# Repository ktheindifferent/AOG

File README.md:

# AOG · Grow observatory

A Raspberry Pi controller for observing a grow system and controlling its equipment. AOG v2 combines a local HTTPS dashboard, air and water sensor history, pH calibration, cameras, schedules, and four assignable relay outputs.

## Dashboard

- **Overview:** air and water temperatures, air quality, pH history, overflow status, and equipment.
- **Connections:** Arduino identification, individual sensor health, pin maps, raw readings, RAM buffer status, and firmware management.
- **Sensor history:** eight metrics with 1-hour, 6-hour, 24-hour, and 7-day views. Water probes keep stable D6/D8 history keys.
- **Reports:** full-resolution CSV/JSON and printable HTML reports, including both water temperatures.
- **Equipment:** independent relays, lighting and watering schedules, configurable overflow stops, and Stop all.

The interface uses local assets and works on desktop and mobile. A reporting Arduino and a physically verified sensor are distinct states. Open overflow contacts can mean high water **or** a disconnected wire; analog pH/gas readings cannot prove physical connection.

## Build and run

Use Rust 1.89 or newer on Raspberry Pi OS / Debian. From the repository root:

```sh
sh setup.sh
cargo build --locked --release -j1
sudo install -m 755 target/release/aog /usr/local/bin/aog-v2.new
sudo mv /usr/local/bin/aog-v2.new /usr/local/bin/aog-v2
sudo install -m 644 deploy/aog-v2.service /etc/systemd/system/aog-v2.service
sudo systemctl daemon-reload
sudo systemctl enable aog-v2
sudo systemctl restart aog-v2
```

Open `https://<pi-address>:8443` and sign in as `admin` using the installation password. Existing settings, passwords, certificates, and recorded data remain in `/opt/aog`. See [controller operation and password recovery](docs/controller.md) and [network configuration](SECURITY.md).

The build automatically embeds current `www/` assets and `firmware/package/`. Rebuilding and installing the controller also installs its firmware package.

## Arduino firmware and water probes

[Sensor Kit](firmware/sensor-kit/sensor-kit.ino) and [Dual OVF](firmware/dual-ovf/dual-ovf.ino) include Nano, Nano old-bootloader, and Uno ATmega328P binaries. Install upload tools on the Pi:

```sh
bash deploy/install-firmware-tools.sh
```

Open **Connections → Firmware**, select the identified Arduino and its actual board profile. AOG pauses schedules, verifies outputs are off, drains supported RAM logs, flashes the checksum-verified package, and waits for the new version to reconnect. Schedules remain paused afterward. Installing AOG or the tools does not flash boards.

The installed three-wire water probes are **not yet identified**. Firmware detects externally powered DS18B20 family `0x28` probes on **D6 and D8 on either Arduino**, verifies CRCs, and exposes each source board and ROM. It does not assume tank assignments. Name and bind probes after identifying them. [Wiring and troubleshooting](docs/wiring.md).

The [Nano carrier PCB](hardware/nano-carrier/README.md) provides removable Nano
sockets, fitted water-probe pull-ups, labeled sensor terminals and CCS811 level
shifting. One common design serves Sensor Kit and Dual OVF. Its prototype
manufacturing/assembly package and small-order instructions are included;
physical hardware qualification is still required.

Each Arduino retains **24 one-minute records in RAM**. The Pi acknowledges a record only after syncing it to disk. Deduplicated replays feed environmental/water history and the pH chart. Original timestamps, raw fields, boot IDs, and sequences can be downloaded from Connections. RAM does not survive resets, flashing, or power loss. A full ring replaces its oldest record and reports drops. USB hardware may reset a board during a Pi reboot even when normal service reconnects preserve it. [Protocol and recovery](docs/firmware-protocol.md).

## Repository

```text
src/                 Rust v2 controller
www/                 Dashboard, local fonts, and vector artwork
firmware/            Arduino sources, build script, tests, and release package
hardware/            Nano carrier PCB, assembly package, and ordering guide
deploy/              systemd service and upload-tool installer
tests/               Backend and browser regression tests
docs/                Operation, wiring, and protocol documentation
```

The Python v1 application, old measurements/media, unused web template, and obsolete notes are removed from the current tree. Previous versions remain in Git history. On-device history schemas remain readable; repository cleanup does not erase runtime data.

[Testing](TESTING.md) · [Firmware builds](firmware/README.md) · [Publishing instructions](docs/publishing.md) · [Existing GitHub repository](https://github.com/PixelCoda/AOG) · [Releases](https://github.com/PixelCoda/AOG/releases)

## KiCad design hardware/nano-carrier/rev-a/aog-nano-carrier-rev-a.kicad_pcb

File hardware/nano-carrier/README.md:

# AOG Nano carrier · revision A

One **80 × 80 mm PCB design**, used twice: plug a Sensor Kit Nano into one
assembled carrier and a Dual OVF Nano into the other. Both carriers use the
same complete parts list, so a two-board order needs only one design and one
assembly setup. Firmware selects the role; there is no hardware mode jumper.

**This is a first prototype design. It has not been manufactured or bench
tested.** Electrical design-rule and connectivity results are in
[rev-a/drc.txt](rev-a/drc.txt) and the release validation file. The water-probe
model and CCS811 breakout remain unidentified; compatibility conditions below
are part of this design, not verified facts about those modules.

## Order the assembled boards

Start with [ORDERING.md](ORDERING.md). Order **two identical, fully populated
carriers**, including the female Nano sockets and screw terminals. The package
contains fabrication Gerbers/drills, a manufacturer-specific BOM, placement
coordinates, editable KiCad files, assembly drawings and a bench-test procedure.
No order has been submitted.

The Nanos and external sensors are reused and are **not included in the
assembly BOM**. The assembler installs the carrier's parts. After delivery you
plug in the Nanos and secure the existing sensor wires in the labeled screw
terminals; factory PCB assembly does not make unidentified sensor cable
harnesses. There is no carrier soldering for you to do. A Nano without soldered
male pins needs those fitted before it can plug into the female sockets.

## Included circuitry

| Circuit | Implementation |
| --- | --- |
| Removable Nano | Two Harwin 1×15 female sockets; 2.54 mm pitch, 15.24 mm between rows |
| Water D6 and D8 | Separate three-wire connectors, each with its own fitted 4.7 kΩ pull-up to 5 V and supply decoupling |
| Overflow D2 and D4 | Dry-contact inputs with 4.7 kΩ pull-ups and 100 nF contact filters |
| Analog A0 | 1 kΩ / 100 nF low-pass filter plus 1 MΩ pull-down; one external pH or CO₂ interface |
| DHT11 D7 | Three-wire connector, fitted 4.7 kΩ data pull-up and supply decoupling |
| CCS811 | Dedicated MCP1700 3.3 V regulator, BSS138 bidirectional SDA/SCL level shifting and four 4.7 kΩ I²C pull-ups |
| CCS811 auxiliary | Two ground terminals for WAKE and ADDR where required by the breakout |
| Power / measurement | USB-derived 5 V, bulk and bypass capacitors, power LED, 5 V/GND/3.3 V/A0 test pads |
| Mounting | Four 3.2 mm non-plated holes, 73 × 73 mm between centers |

The 1 MΩ analog pull-down reduces floating values when the **interface cable**
is absent. It cannot detect an unplugged electrode on a powered Gravity pH
board. AOG's physical-connection confirmation and calibration still apply.
The analog filter introduces approximately 0.1% DC attenuation with a low
impedance source; recalibrate pH after fitting the carrier.

## Compatible hardware and power

- Classic **5 V / 16 MHz ATmega328P Nano**, including matching old-bootloader
  clones with the standard 30-pin footprint. USB points toward the top edge.
  Nano 33, RP2040, ESP32 and other 3.3 V boards are not interchangeable here.
- Water connectors expect **externally powered DS18B20** probes. Probe colors
  are not a pinout. Identify VDD, DQ and GND before connecting. A three-wire
  thermistor or RTD does not become compatible by adding a pull-up.
- CCS811 connector J9 supplies **3.3 V**, with 3.3 V I²C logic. Use a breakout
  documented to work at 3.3 V and address **0x5A**. The actual breakout brand is
  unknown; this design deliberately does not send 5 V into its I²C pins.
  A bare CCS811 chip needs its own support circuit and is not a plug-in module.
  Keep the I²C harness short (target 20 cm or less). Existing breakout pull-ups
  remain in parallel; check SDA/SCL rise times if the connection is unreliable.
- J5 accepts the **Atlas Gravity V2.1 analog pH board** on the Dual OVF carrier,
  or the **DFRobot SEN0219 v1 analog CO₂ module** on Sensor Kit. The pH electrode
  stays connected to its Gravity board. SEN0219 v2 PWM is not supported by this
  analog path or the current analog firmware profile.
- J6 expects the installed firmware's **DHT11**, not DHT22 or an I²C replacement.
- Overflow switches must be voltage-free contacts, closed to ground when safe.
  No pumps, relays, mains, 12 V or 24 V circuits attach to these connectors.

Power comes from each **Nano's USB connection**. VIN, AREF and the Nano's 3V3
pin are deliberately unconnected. There is no external power-input terminal;
do not inject power into a sensor output connector while USB is connected.
The carrier does not regulate the nominal 5 V rail: actual voltage depends on
the Nano's USB diode, cable and USB source. In particular, verify the CO₂
module's rated supply range under load. If it requires 5.0 ±0.1 V and the
Nano rail cannot deliver that, the power arrangement needs revision before
using that module; this carrier does not correct undervoltage or ADC-reference
error.

Use a conservative total external-sensor budget of **250 mA on the Nano 5 V
rail**, including the regulator input, and **100 mA maximum from the carrier's
3.3 V output**. These are design limits, not promises about an unidentified
Nano clone's USB power path. Verify its rating and the combined sensor peak
current. The 3.3 V regulator is not galvanic isolation, and the carriers are
not waterproof; mount them in a dry enclosure with cable strain relief.

## Which connector to use

Pad numbers are defined in the CAD files; follow the printed **signal labels**
when connecting wires. Right-side connector order appears reversed in a top
view because those connectors face the opposite board edge.

| Connector | Pin 1 | Pin 2 | Pin 3 | Pin 4 | Role |
| --- | --- | --- | --- | --- | --- |
| J3 · WATER D6 | 5 V / probe VDD | D6 / probe DQ | GND | — | Either |
| J4 · WATER D8 | 5 V / probe VDD | D8 / probe DQ | GND | — | Either |
| J5 · ANALOG A0 | 5 V / `+` | Analog signal / `A` | GND / `−` | — | pH on Dual OVF; analog CO₂ on Sensor Kit |
| J6 · DHT11 D7 | 5 V | DATA / D7 | GND | — | Sensor Kit |
| J7 · OVERFLOW D2 | Contact / D2 | GND | — | — | Dual OVF |
| J8 · OVERFLOW D4 | Contact / D4 | GND | — | — | Dual OVF |
| J9 · CCS811 | 3.3 V supply | GND | SDA | SCL | Sensor Kit |
| J10 · WAKE / ADDR | GND for WAKE | GND for ADDR | — | — | Sensor Kit, if the breakout needs these leads |

J9 is a labeled wire connector, **not a standardized CCS811 plug footprint**.
Map the breakout's printed pin names; do not plug a random four-pin cable in
based on color or presumed pin order. A reset pin, if exposed, follows the
breakout manufacturer's reset/pull-up requirements.

Keep the same probe-to-Arduino assignment as today. The current firmware
already checks D6 and D8 on both boards; moving the probes may require updating
their bindings in AOG. A water connector on the second board is optional, not
an instruction to install two probes on the same bus.

## Files and reproduction

- `rev-a/aog-nano-carrier-rev-a.kicad_pro`: editable KiCad project.
- `rev-a/aog-nano-carrier-rev-a.kicad_sch`: editable, embedded-symbol schematic.
- `rev-a/aog-nano-carrier-rev-a.kicad_pcb`: routed two-layer PCB.
- `rev-a/manufacturing/`: Gerber layers and separate plated/non-plated drills.
- `rev-a/bom.csv`, `positions.csv`, `assembly.pdf`: assembly inputs.
- `rev-a/board-1-to-1.pdf`: 80 × 80 mm print for a physical Nano/header fit check;
  print at actual size and measure it, with page scaling disabled.
- `rev-a/connections-*.pdf`: readable per-circuit pin references.
- `rev-a/preview.html`: offline connector guide for the two firmware roles.
- `rev-a/drc.txt`, `validation.json`: actual release-check results.
- `ASSEMBLY.md`: factory instructions and prototype bring-up.
- `SOURCES.md`: manufacturer references and footprint provenance.

On Debian 12 with KiCad 6.0.11, `kicad-footprints`, `kicad-symbols`,
`python3-numpy`, `python3-cairosvg` and `xvfb` installed:

```sh
xvfb-run -a python3 hardware/nano-carrier/tools/build.py
python3 hardware/nano-carrier/tools/documents.py
# Open the saved schematic in KiCad and run Inspect > Electrical Rules Checker.
# Save its zero-error/zero-warning report as rev-a/erc.txt and record the checked
# schematic/report hashes in erc-verification.json. Recheck after any edit.
python3 hardware/nano-carrier/tools/release.py
```

The release script refuses to package a PCB with DRC violations or unconnected
pads, or a schematic without a matching successful ERC report. Build outputs
are deterministic in electrical content;
KiCad timestamps and internal generated UUIDs may vary. No controller code,
Arduino firmware or production service needs to change to use these carriers.

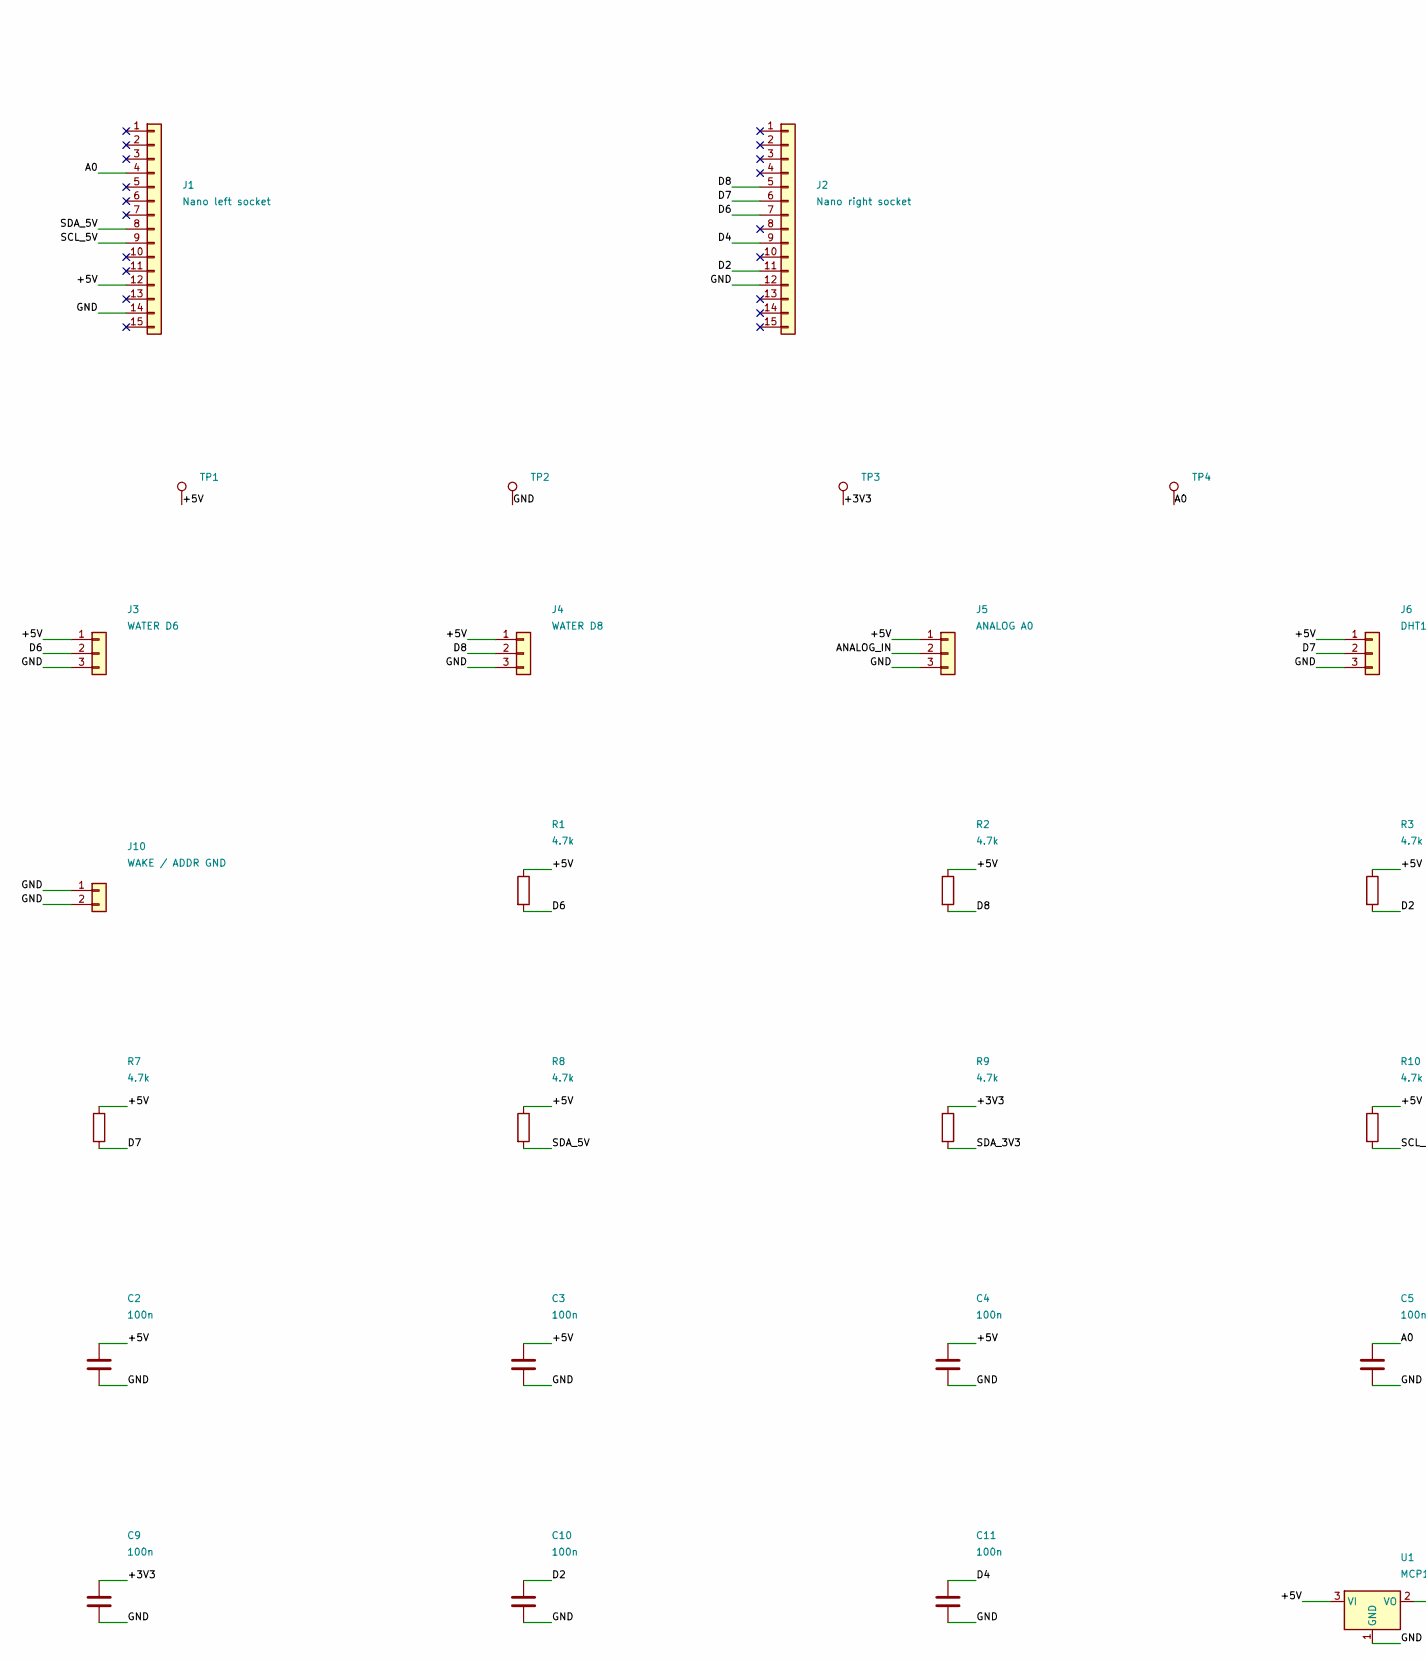
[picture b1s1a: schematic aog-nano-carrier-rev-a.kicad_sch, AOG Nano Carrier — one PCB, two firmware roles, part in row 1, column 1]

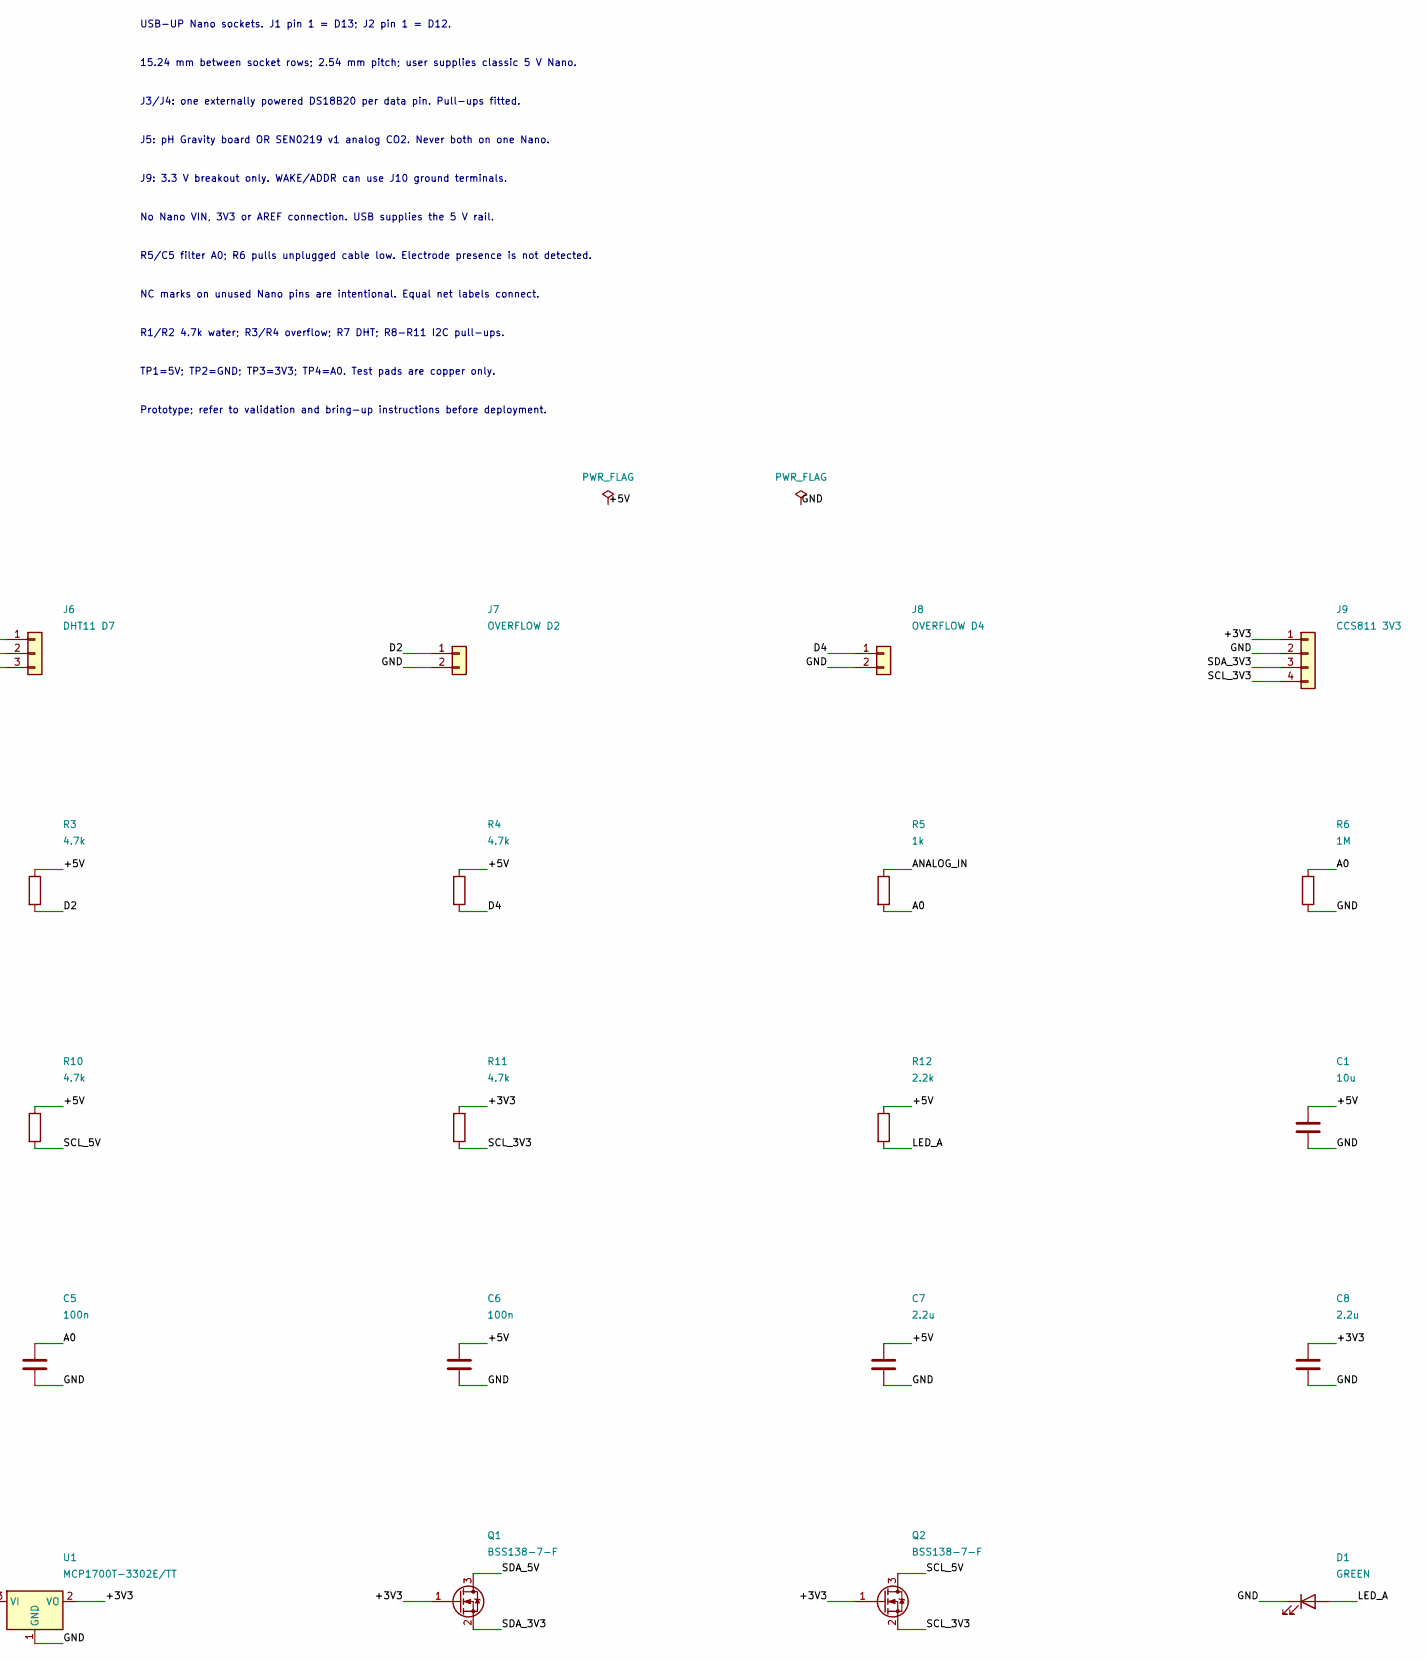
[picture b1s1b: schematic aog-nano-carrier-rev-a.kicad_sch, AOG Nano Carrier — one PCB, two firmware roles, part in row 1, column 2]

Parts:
C1: 10u; C_0805_2012Metric
C2, C3, C4, C5, C6, C9, C10, C11: 100n; C_0805_2012Metric
C7, C8: 2.2u; C_0805_2012Metric
D1: GREEN; LED_0805_2012Metric
J1: Nano left socket; PinSocket_1x15_P2.54mm_Vertical
J2: Nano right socket; PinSocket_1x15_P2.54mm_Vertical
J3: WATER D6; TerminalBlock_METZ_RT03403HBLC_P3.81_Drill1.1
J4: WATER D8; TerminalBlock_METZ_RT03403HBLC_P3.81_Drill1.1
J5: ANALOG A0; TerminalBlock_METZ_RT03403HBLC_P3.81_Drill1.1
J6: DHT11 D7; TerminalBlock_METZ_RT03403HBLC_P3.81_Drill1.1
J7: OVERFLOW D2; TerminalBlock_METZ_RT03402HBLC_P3.81_Drill1.1
J8: OVERFLOW D4; TerminalBlock_METZ_RT03402HBLC_P3.81_Drill1.1
J9: CCS811 3V3; TerminalBlock_METZ_RT03404HBLC_P3.81_Drill1.1
J10: WAKE / ADDR GND; TerminalBlock_METZ_RT03402HBLC_P3.81_Drill1.1
Q1, Q2: BSS138-7-F; SOT-23
R1, R2, R3, R4, R7, R8, R9, R10, R11: 4.7k; R_0805_2012Metric
R5: 1k; R_0805_2012Metric
R6: 1M; R_0805_2012Metric
R12: 2.2k; R_0805_2012Metric
TP1: +5V; TestPoint_Pad_D1.5mm
TP2: GND; TestPoint_Pad_D1.5mm
TP3: +3V3; TestPoint_Pad_D1.5mm
TP4: A0; TestPoint_Pad_D1.5mm
U1: MCP1700T-3302E/TT; SOT-23

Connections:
+3V3: C8.1, C9.1, J9.1, Q1.1 (G), Q2.1 (G), R9.1, R11.1, TP3.1, U1.2 (VO)
+5V: C1.1, C2.1, C3.1, C4.1, C6.1, C7.1, J1.12, J3.1, J4.1, J5.1, J6.1, R1.1, R2.1, R3.1, R4.1, R7.1, R8.1, R10.1, R12.1, TP1.1, U1.3 (VI)
A0: C5.1, J1.4, R5.2, R6.1, TP4.1
ANALOG_IN: J5.2, R5.1
D2: C10.1, J2.11, J7.1, R3.2
D4: C11.1, J2.9, J8.1, R4.2
D6: J2.7, J3.2, R1.2
D7: J2.6, J6.2, R7.2
D8: J2.5, J4.2, R2.2
GND: C1.2, C2.2, C3.2, C4.2, C5.2, C6.2, C7.2, C8.2, C9.2, C10.2, C11.2, D1.1 (K), J1.14, J2.12, J3.3, J4.3, J5.3, J6.3, J7.2, J8.2, J9.2, J10.1, J10.2, R6.2, TP2.1, U1.1 (GND)
LED_A: D1.2 (A), R12.2
NC_3V3: J1.2
NC_A1: J1.5
NC_A2: J1.6
NC_A3: J1.7
NC_A6: J1.10
NC_A7: J1.11
NC_AREF: J1.3
NC_D3: J2.10
NC_D5: J2.8
NC_D9: J2.4
NC_D10: J2.3
NC_D11: J2.2
NC_D12: J2.1
NC_D13: J1.1
NC_RESET_L: J1.13
NC_RESET_R: J2.13
NC_RX: J2.14
NC_TX: J2.15
NC_VIN: J1.15
SCL_3V3: J9.4, Q2.2 (S), R11.2
SCL_5V: J1.9, Q2.3 (D), R10.2
SDA_3V3: J9.3, Q1.2 (S), R9.2
SDA_5V: J1.8, Q1.3 (D), R8.2

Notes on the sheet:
USB-UP Nano sockets. J1 pin 1 = D13; J2 pin 1 = D12.
15.24 mm between socket rows; 2.54 mm pitch; user supplies classic 5 V Nano.
J3/J4: one externally powered DS18B20 per data pin. Pull-ups fitted.
J5: pH Gravity board OR SEN0219 v1 analog CO2. Never both on one Nano.
J9: 3.3 V breakout only. WAKE/ADDR can use J10 ground terminals.
No Nano VIN, 3V3 or AREF connection. USB supplies the 5 V rail.
R5/C5 filter A0; R6 pulls unplugged cable low. Electrode presence is not detected.
NC marks on unused Nano pins are intentional. Equal net labels connect.
R1/R2 4.7k water; R3/R4 overflow; R7 DHT; R8-R11 I2C pull-ups.
TP1=5V; TP2=GND; TP3=3V3; TP4=A0. Test pads are copper only.
Prototype; refer to validation and bring-up instructions before deployment.

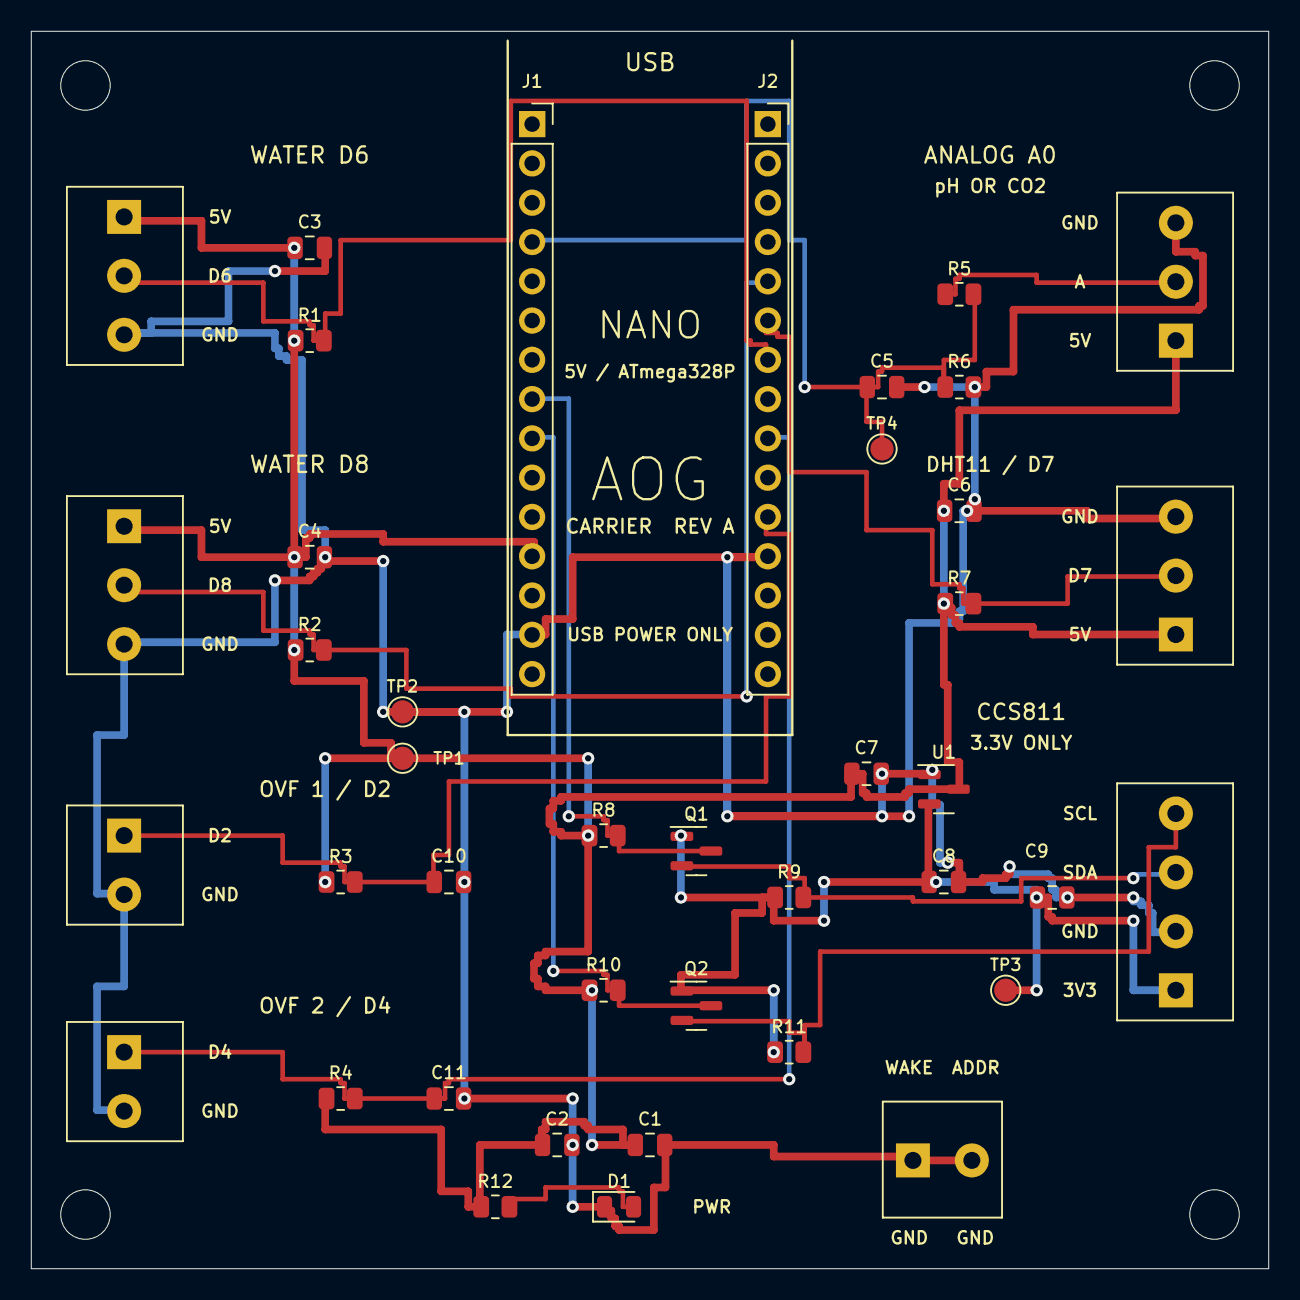
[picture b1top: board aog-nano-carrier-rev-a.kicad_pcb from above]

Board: 2 copper layers, 80.0 x 80.0 mm, 45 parts (0 on the bottom side), 15 nets.

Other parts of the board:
H1, H2, H3, H4: M3 NPTH; MountingHole_3.2mm_M3

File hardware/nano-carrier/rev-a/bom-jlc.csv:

Comment,Designator,Footprint,LCSC Part #,Manufacturer,Manufacturer Part Number
Nano left socket,J1,Connector_PinSocket_2.54mm:PinSocket_1x15_P2.54mm_Vertical,,Harwin,M20-7821546
Nano right socket,J2,Connector_PinSocket_2.54mm:PinSocket_1x15_P2.54mm_Vertical,,Harwin,M20-7821546
WATER D6,J3,AOG:TerminalBlock_METZ_RT03403HBLC_P3.81_Drill1.1,,METZ CONNECT,RT03403HBLC
WATER D8,J4,AOG:TerminalBlock_METZ_RT03403HBLC_P3.81_Drill1.1,,METZ CONNECT,RT03403HBLC
ANALOG A0,J5,AOG:TerminalBlock_METZ_RT03403HBLC_P3.81_Drill1.1,,METZ CONNECT,RT03403HBLC
DHT11 D7,J6,AOG:TerminalBlock_METZ_RT03403HBLC_P3.81_Drill1.1,,METZ CONNECT,RT03403HBLC
OVERFLOW D2,J7,AOG:TerminalBlock_METZ_RT03402HBLC_P3.81_Drill1.1,,METZ CONNECT,RT03402HBLC
OVERFLOW D4,J8,AOG:TerminalBlock_METZ_RT03402HBLC_P3.81_Drill1.1,,METZ CONNECT,RT03402HBLC
CCS811 3V3,J9,AOG:TerminalBlock_METZ_RT03404HBLC_P3.81_Drill1.1,,METZ CONNECT,RT03404HBLC
WAKE / ADDR GND,J10,AOG:TerminalBlock_METZ_RT03402HBLC_P3.81_Drill1.1,,METZ CONNECT,RT03402HBLC
4.7k,R1,Resistor_SMD:R_0805_2012Metric,,Yageo,RC0805FR-074K7L
4.7k,R2,Resistor_SMD:R_0805_2012Metric,,Yageo,RC0805FR-074K7L
4.7k,R3,Resistor_SMD:R_0805_2012Metric,,Yageo,RC0805FR-074K7L
4.7k,R4,Resistor_SMD:R_0805_2012Metric,,Yageo,RC0805FR-074K7L
1k,R5,Resistor_SMD:R_0805_2012Metric,,Yageo,RC0805FR-071KL
1M,R6,Resistor_SMD:R_0805_2012Metric,,Yageo,RC0805FR-071ML
4.7k,R7,Resistor_SMD:R_0805_2012Metric,,Yageo,RC0805FR-074K7L
4.7k,R8,Resistor_SMD:R_0805_2012Metric,,Yageo,RC0805FR-074K7L
4.7k,R9,Resistor_SMD:R_0805_2012Metric,,Yageo,RC0805FR-074K7L
4.7k,R10,Resistor_SMD:R_0805_2012Metric,,Yageo,RC0805FR-074K7L
4.7k,R11,Resistor_SMD:R_0805_2012Metric,,Yageo,RC0805FR-074K7L
2.2k,R12,Resistor_SMD:R_0805_2012Metric,,Yageo,RC0805FR-072K2L
10u,C1,Capacitor_SMD:C_0805_2012Metric,,Murata,GRM21BR61E106KA73L
100n,C2,Capacitor_SMD:C_0805_2012Metric,,Murata,GRM21BR71E104KA01L
100n,C3,Capacitor_SMD:C_0805_2012Metric,,Murata,GRM21BR71E104KA01L
100n,C4,Capacitor_SMD:C_0805_2012Metric,,Murata,GRM21BR71E104KA01L
100n,C5,Capacitor_SMD:C_0805_2012Metric,,Murata,GRM21BR71E104KA01L
100n,C6,Capacitor_SMD:C_0805_2012Metric,,Murata,GRM21BR71E104KA01L
2.2u,C7,Capacitor_SMD:C_0805_2012Metric,,Murata,GRM21BR71E225KA73L
2.2u,C8,Capacitor_SMD:C_0805_2012Metric,,Murata,GRM21BR71E225KA73L
100n,C9,Capacitor_SMD:C_0805_2012Metric,,Murata,GRM21BR71E104KA01L
100n,C10,Capacitor_SMD:C_0805_2012Metric,,Murata,GRM21BR71E104KA01L
100n,C11,Capacitor_SMD:C_0805_2012Metric,,Murata,GRM21BR71E104KA01L
MCP1700T-3302E/TT,U1,Package_TO_SOT_SMD:SOT-23,,Microchip,MCP1700T-3302E/TT
BSS138-7-F,Q1,Package_TO_SOT_SMD:SOT-23,,Diodes Incorporated,BSS138-7-F
BSS138-7-F,Q2,Package_TO_SOT_SMD:SOT-23,,Diodes Incorporated,BSS138-7-F
GREEN,D1,LED_SMD:LED_0805_2012Metric,,Lite-On,LTST-C170KGKT

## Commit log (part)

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2021-07-17 init
2021-07-20 parts list
2021-07-20 roadmap
2021-08-16 rust-alpha
2021-08-16 rust v2 bones
2021-08-23 web cam and updates for 0.2.0
2021-08-23 added install/uninstall cli args
2021-08-23 added gpio stress test cli arg to fix a stuck relay
2021-08-27 experimenting with stopable threads
2021-08-29 logging
2021-08-29 debugin
2021-08-31 cleaner, more comments, and better control threads for gpio relays
2021-09-01 support for multiple program instances via unified https command gateway
2021-09-01 debuggin
2025-08-09 fix(aog): improve error handling and logging in command, http, sensors, video
    - Added error handling and logging for GPIO pin parsing in command.rs
    - Disabled infinite loop in test command with info log
    - Added error handling for relay commands without unwrap
    - Improved HTTPS server startup error handling in http.rs
    - Added command whitelist and validation in command API
    - Added error handling for file operations in sensors.rs
2025-08-10 chore: add empty git diff for commit message generation
2025-08-10 feat(docs): add comprehensive project overview and description
    - Added overview.md with detailed system architecture, flow diagrams, and module descriptions
    - Added project_description.md summarizing project goals, technology stack, components, and current status
    - Updated command.rs import for improved IO handling
    - Added extensive tests in lib.rs for configuration, sessions, and sensor logs
    - Created todo.md listing development tasks, priorities, and next steps
    These additions improve project documentation, testing coverage, and development planning.
2025-08-15 docs(documentation): add comprehensive project documentation file CLAUDE.md
    Added a detailed documentation file CLAUDE.md that provides an extensive overview of the A.O.G. (Algae Oxygen Reactor) project. This includes repository structure, technology stack, system architectu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
2025-08-17 feat(overflow-safety): add overflow detection and safety handling for pumps
    - Introduced new API endpoint /api/alerts/overflow to report overflow alerts and sensor errors.
    - Enhanced pump control logic to block operation if overflow conditions or sensor errors are detected.
    - Implemented critical safety measures to set overflow sensor states to OVERFLOW on serial communication failures.
    - Added recovery logic to clear error state upon successful sensor communication.
    - Extended /api/stats endpoint to include overflow sensor states and error presence.
    - Added comprehensive tests for overflow sensor failure, recovery, and critical condition detection.
2025-08-17 feat(qwiic): add automatic recovery and health monitoring for Qwiic relay
    - Introduce RecoveryConfig to configure auto recovery, system reboot, retry attempts, health check interval, and alert webhook
    - Implement RelayError enum for detailed error handling
    - Add RelayHealthStatus to track health state, failures, firmware version, and last error
    - Implement retry mechanism with exponential backoff for relay operations
    - Add firmware version compatibility check
    - Add health monitoring thread with periodic checks
2025-08-17 test(aog/sensors): add comprehensive unit tests for Arduino sensor parsing
    - Added multiple unit tests for parse_arduino function covering valid, malformed, empty, multiple values, special characters, and edge cases.
    - Added tests for get_value function for existing and missing sensor files.
    - Added tests for fetch_pm25 and fetch_pm10 functions when no device is present.
    - Introduced test setup helper to create temporary sensor directories.
    - Added dev dependencies for mocking, property testing, async testing, serial test, tempfile, and assert matches.
    This improves test coverage and robustness of sensor data parsing and retrieval logic.
2025-08-17 refactor(error-handling): improve error handling and add tests for robustness
    - Replace unwrap and expect calls with proper error handling and logging
    - Modify Config and Sessions save/load methods to return Result and handle errors gracefully
    - Add extensive error handling tests to verify system stability under failure conditions
    - Update command execution functions to return errors instead of panicking
    - Improve file extraction and setup functions with error propagation and logging
    - Enhance main input reading with error handling
2025-08-17 refactor(error-handling): replace unwrap/expect with proper error handling and logging
    - Replaced all unwrap() and expect() calls with match statements or if let constructs
    - Added error logging for failures in Qwiic relay initialization and GPIO thread locking
    - Improved robustness by preventing panics and enabling graceful error recovery
    - Added detailed error handling summary in ERROR_HANDLING_IMPROVEMENTS.md
    This refactor enhances system reliability by avoiding panics and providing better error context.
2025-08-17 feat(qwiic): add automatic recovery mechanism for Qwiic relay device
    - Implemented comprehensive automatic recovery with firmware version checking, retry with exponential backoff, system reboot fallback, health monitoring, and alerting.
    - Added new example test_relay_recovery.rs demonstrating usage and configuration.
    - Introduced RecoveryConfig for customizable recovery parameters.
    - Added detailed implementation summary documentation.
    - Refactored qwiic.rs to integrate recovery features and improve relay state handling.
    - Updated lib.rs to re-export QwiicRelayDevice and related types for easier access.
2025-08-17 feat(testing): add comprehensive testing infrastructure and CI pipeline
    - Introduce GitHub Actions workflow for Rust tests including format check, linting, build, unit, integration, doc, property tests, coverage, and security audit
    - Add TESTING.md with detailed testing strategy, guidelines, and local run instructions
    - Add TEST_COVERAGE_SUMMARY.md summarizing test coverage, dependencies, and next steps
    - Add extensive unit tests for pump and qwiic modules
    - Add integration tests covering config lifecycle, sensor logs, sessions, and overflow detection
    - Add property-based tests for sensor logs, config, and session properties
2025-08-17 feat(pump control): add continuous mode, photo cycle, and safety GPIO features
    - Introduce continuous operation mode for pumps to run bypassing sensor control
    - Add photo cycle scheduling to sync pump operation with light schedules
    - Implement safety GPIO pin monitoring to block pump operation on unsafe conditions
    - Add runtime limits and cooldown periods to prevent pump burnout
    - Update pump thread and config structures with new fields
    - Enhance pump logic to respect new modes and safety checks
2025-08-30 feat(network-security): bind servers to localhost by default for improved security
    - Changed HTTPS and Command API servers to bind to 127.0.0.1 by default instead of 0.0.0.0
    - Added configuration options for HTTPS and Command API bind addresses and ports
    - Added logging for server bind addresses
    - Added SECURITY.md with detailed security configuration and best practices
    - Added NETWORK_SECURITY_FIX_SUMMARY.md summarizing the security fix
    - Added test_network_security.sh script to verify server accessibility
2025-08-30 feat(auth): implement secure password handling and authentication
    - Replace hardcoded admin password with Argon2 hashed passwords
    - Add password hashing, verification, and strength validation
    - Generate cryptographically secure random passwords
    - Update setup to generate and display initial secure password
    - Modify HTTP auth to verify hashed passwords securely
    - Add comprehensive authentication integration tests
2025-08-30 fix(security): fix file permissions and harden service user
    - Remove dangerous 777 permissions, set secure permissions by file type
    - Add functions to set ownership, validate and fix permissions
    - Create dedicated 'aog' user and group with no shell access
    - Harden systemd service with security options and run as 'aog' user
    - Validate and fix permissions on startup with audit logging
    - Add test script to verify permission security
2025-08-30 feat(pump_safety): add comprehensive pump safety system with monitoring and controls
    - Introduced PumpSafetyMonitor module for runtime limits, oscillation safety, emergency shutdown, cooldown periods, and maintenance tracking
    - Added detailed pump safety states and event logging
    - Implemented safety checks integrated into pump operation logic
    - Added calibration routines and configuration persistence
    - Created extensive safety documentation (PUMP_SAFETY_DOCUMENTATION.md)
    - Updated Cargo.toml and dependencies for lazy_static
2025-08-30 feat(error-handling): add comprehensive error handling and monitoring system
    - Introduce AogError enum with detailed error variants and recovery info
    - Add ErrorContext struct for enriched error context logging
    - Implement log_error_with_context for structured error logging
    - Create ErrorMonitor for tracking, storing, and reporting errors
    - Add error monitoring dashboard API endpoint
    - Integrate error handling and logging in pump module and main HTTP response
2025-08-31 feat(water_level): add water level sensor module with integration and tests
    - Introduce a new water level sensor module supporting ultrasonic and mock sensors
    - Implement WaterLevelMonitor and WaterLevelSystem for real-time monitoring
    - Integrate water level readings into pump safety checks and calibration
    - Add configuration options for water level sensors in the main config
    - Initialize water level system in main application startup
    - Provide fallback to overflow sensors if primary sensors fail
2025-08-31 feat(ph_sensor): add pH sensor support with monitoring and UI integration
    - Introduce a new pH sensor module with calibration, reading, history, and alerting
    - Add pH sensor initialization and monitoring in sensors module
    - Extend config with pH sensor configuration options
    - Update HTTP API to include pH sensor data and status
    - Add UI elements and JS code to display pH value, trend, and adjustment suggestions
    - Include comprehensive tests for pH sensor functionality and calibration
2025-08-31 feat(error): add comprehensive error handling and recovery for mutex poisoning
    - Introduce AogError enum for detailed error categorization
    - Implement conversion traits for common error types
    - Provide recover_mutex_lock and safe_mutex_access helpers for mutex poisoning recovery
    - Refactor pump safety module to use safe mutex access and error handling
    - Improve HTTP config locking with error handling
    - Add extensive tests for error handling, mutex recovery, and pump safety
